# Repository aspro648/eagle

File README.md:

Repository to hold Eagle Cad design files I'm working on and sharing.

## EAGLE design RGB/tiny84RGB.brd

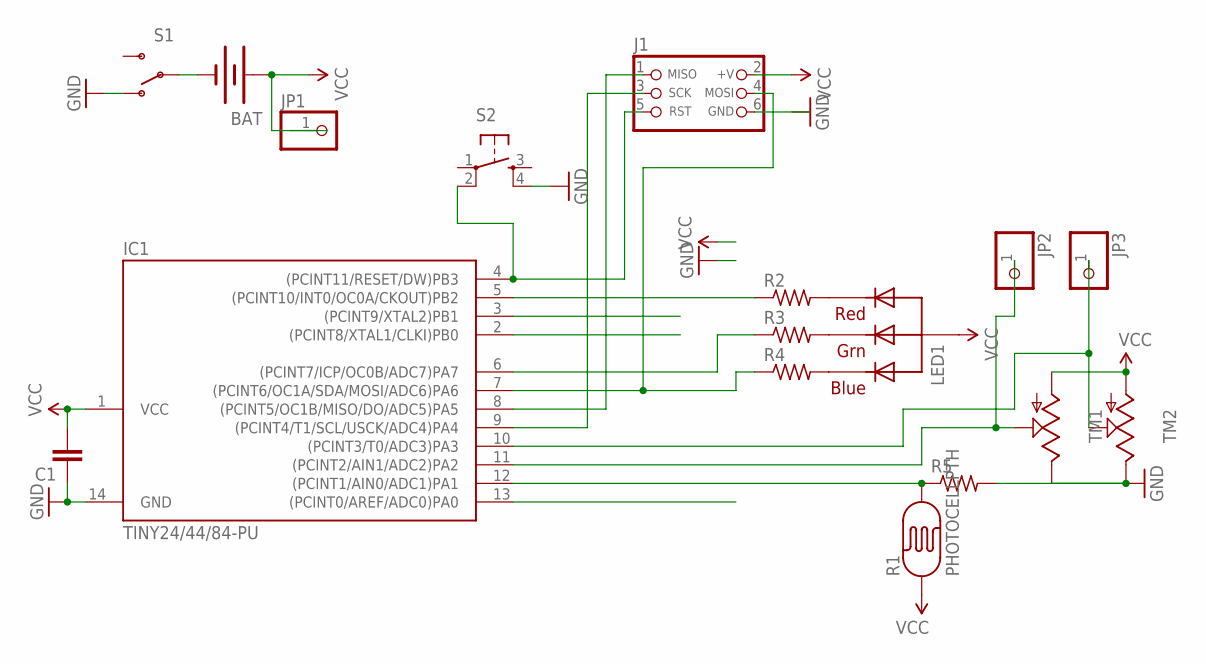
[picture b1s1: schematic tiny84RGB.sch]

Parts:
BAT: BATTERY20PTH; BATTCOM_20MM_PTH
C1: CAPKIT; CAP-PTH-SMALL-KIT
IC1: TINY24/44/84-PU; DIL14
J1: CON_HEADER_PRG_AVR_ICSP-PTH; HEADER_PRG_2X03
JP1, JP2, JP3: PINHD-1X1CB; 1X01-CLEANBIG
LED1: RGBLED_CA-5MM; LED5MMRGB
R1: PHOTOCELLPTH; PHOTOCELL
R2, R3, R4, R5: R-US_0204/7; 0204/7
S1: SWITCH-SPSTPTH; SWITCH-SPDT
S2: TAC_SWITCHPTH; TACTILE-PTH
TM1, TM2: TRIM; 6MM

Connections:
D0: IC1.13 ((PCINT0/AREF/ADC0)PA0)
D1: IC1.12 ((PCINT1/AIN0/ADC1)PA1), R1.2, R5.1
D2: IC1.11 ((PCINT2/AIN1/ADC2)PA2), JP2.1, TM1.S
D3: IC1.10 ((PCINT3/T0/ADC3)PA3), JP3.1, TM2.S
D4: IC1.9 ((PCINT4/T1/SCL/USCK/ADC4)PA4), J1.3 (SCK)
D5: IC1.8 ((PCINT5/OC1B/MISO/DO/ADC5)PA5), J1.1 (MISO)
D6: IC1.7 ((PCINT6/OC1A/SDA/MOSI/ADC6)PA6), J1.4 (MOSI), R4.1
D7: IC1.6 ((PCINT7/ICP/OC0B/ADC7)PA7), R3.1
D9: IC1.3 ((PCINT9/XTAL2)PB1)
D10: IC1.2 ((PCINT8/XTAL1/CLKI)PB0)
GND: C1.1, IC1.14 (GND), R5.2, S1.1 (O), S2.4, TM1.E, TM2.E
unnamed: BAT.2 (-), S1.2
unnamed: LED1.1 (RED), R2.2
unnamed: LED1.3 (GREEN), R3.2
unnamed: LED1.4 (BLUE), R4.2
unnamed: IC1.5 ((PCINT10/INT0/OC0A/CKOUT)PB2), R2.1
RESET: IC1.4 ((PCINT11/RESET/DW)PB3), J1.5 (RST), S2.2
VCC: BAT.1 (+), C1.2, IC1.1 (VCC), J1.2 (+V), JP1.1, LED1.2 (VCC), R1.1, TM1.A, TM2.A

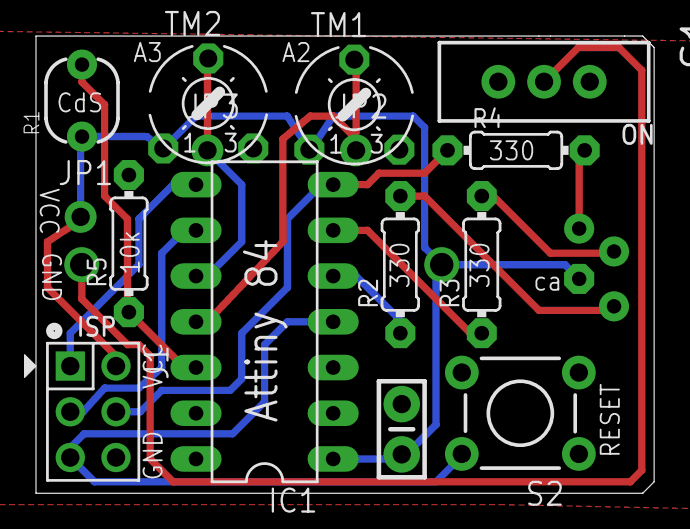
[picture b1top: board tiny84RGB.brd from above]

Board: 2 copper layers, 34.3 x 25.4 mm, 18 parts (1 on the bottom side), 15 nets.

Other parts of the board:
U$1: OREGON_18_52

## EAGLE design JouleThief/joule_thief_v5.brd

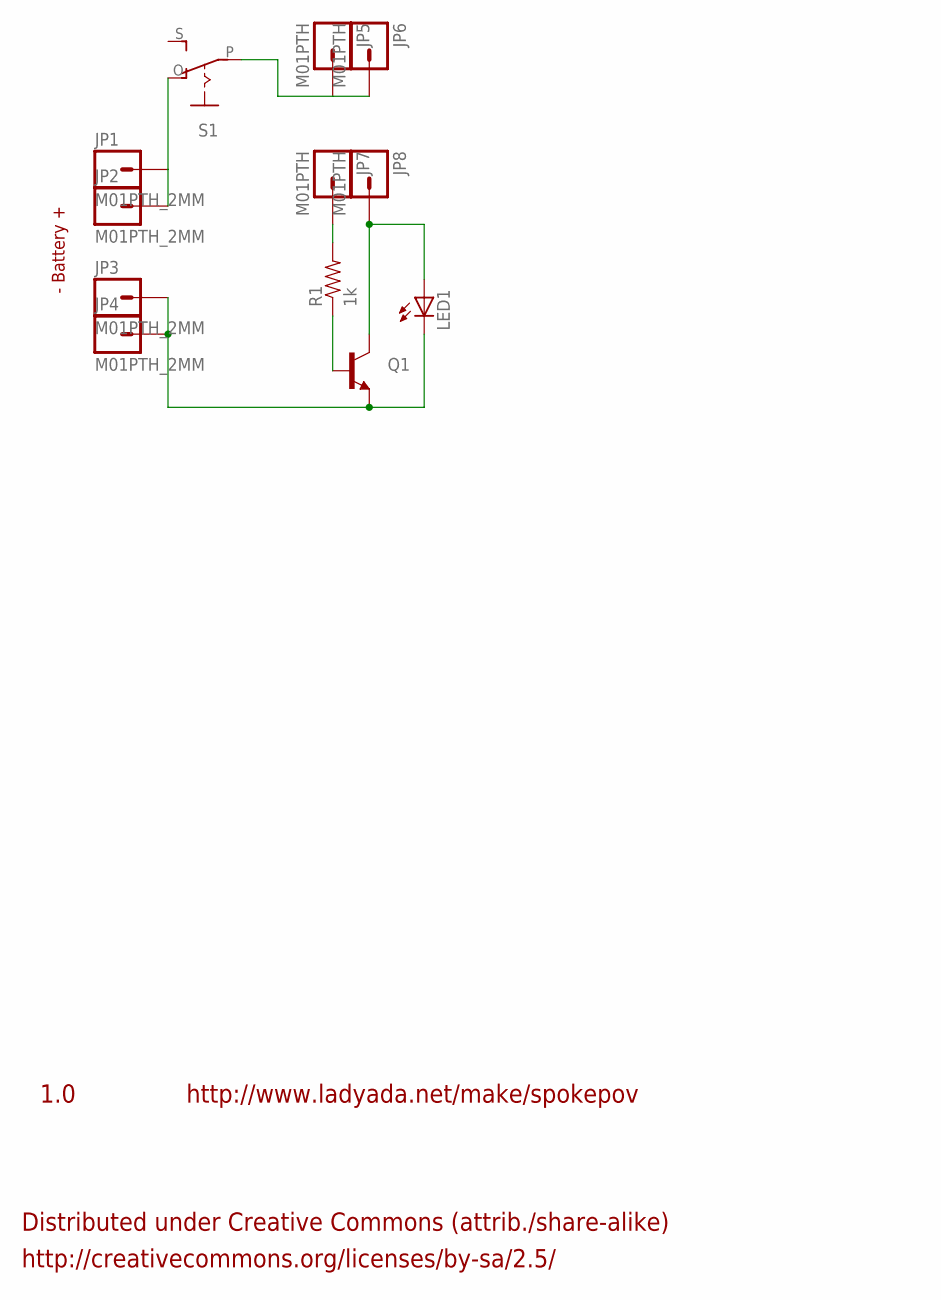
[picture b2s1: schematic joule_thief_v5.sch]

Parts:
JP1, JP2, JP3, JP4: M01PTH_2MM; 1X01_2MM
JP5, JP6, JP7, JP8: M01PTH; 1X01
LED1: LED5MM
Q1: TRANSISTOR_NPNTO-92-AMMO; TO-92-AMMO
R1: 1k; AXIAL-0.3
S1: EG1218S; EG1218

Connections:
unnamed: JP8.1, LED1.A, Q1.3 (C)
unnamed: JP7.1, R1.P$2 (2)
unnamed: Q1.2 (B), R1.P$1 (1)
unnamed: JP1.1, JP2.1, S1.O
unnamed: JP5.1, JP6.1, S1.P
unnamed: JP3.1, JP4.1, LED1.K (C), Q1.1 (E)

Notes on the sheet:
1.0
http://creativecommons.org/licenses/by-sa/2.5/
http://www.ladyada.net/make/spokepov
Distributed under Creative Commons (attrib./share-alike)
- Battery +

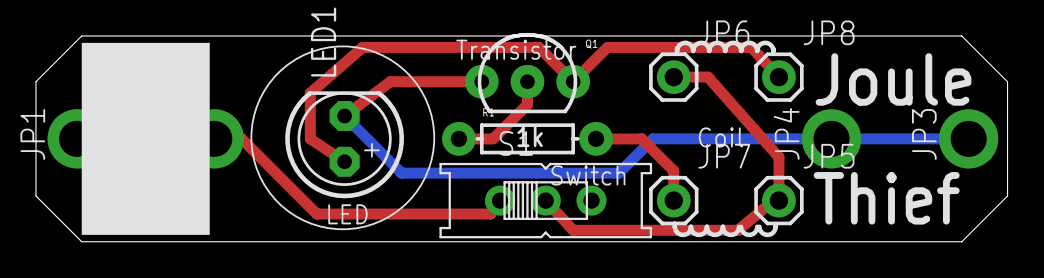
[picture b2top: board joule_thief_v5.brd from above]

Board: 2 copper layers, 54.0 x 11.4 mm, 12 parts (0 on the bottom side), 6 nets.

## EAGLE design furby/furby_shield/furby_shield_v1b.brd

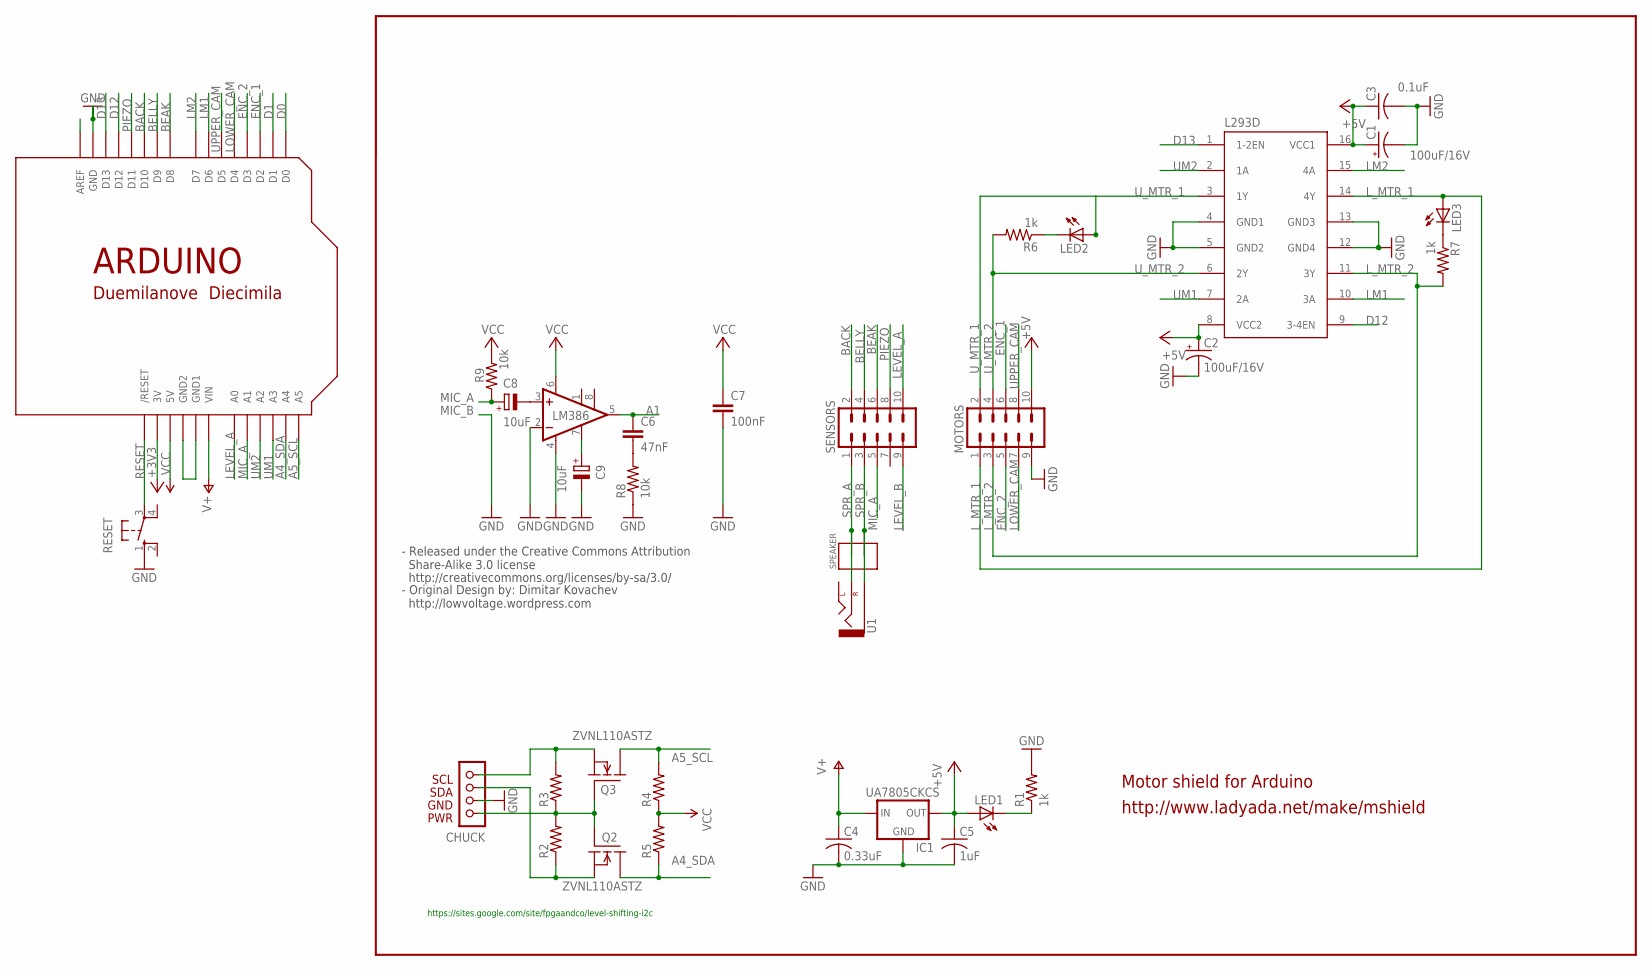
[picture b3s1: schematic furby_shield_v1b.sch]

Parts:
C1, C2: 100uF/16V; E2,5-6
C3: 0.1uF; C025-025X050
C4: 0.33uF; C025-024X044
C5: 1uF; C025-024X044
C6: 47nF; C025-030X050
C7: 100nF; C025-025X050
C8, C9: 10uF; E2,5-6
CHUCK: NUNCHUCK; CONN
IC1: UA7805CKCS; TO-220-ALT
L293D: L293E; DIL16
LED1, LED2, LED3: LED3MM
LM386: LM386N-1; DIL08
MOTORS: M05X2SHD; 2X5-SHROUDED
Q2, Q3: ZVNL110ASTZ; TO92-INLINE
R1, R6, R7: 1k; 0204/5
R2, R3, R4, R5: R-US_0204/7; 0204/7
R8, R9: 10k; 0204/7
RESET: 10-XX; B3F-10XX
SENSORS: M05X2SHD; 2X5-SHROUDED
SPEAKER: TERMINAL2; TERMINAL_2
U1: AUDIO-JACKPTH; AUDIO-JACK
U$1: ARDUINO-NOHOLE

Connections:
+3V3: CHUCK.PWR, Q2.2 (G), Q3.2 (G), R2.2, R3.1, U$1.3V
+5V: C1.+, C2.+, C3.1, C5.1, IC1.OUT, L293D.8 (VCC2), L293D.16 (VCC1), LED1.A, MOTORS.10
A1: C6.1, LM386.5 (OUT)
A4_SDA: Q2.1 (D), R5.1, U$1.A4
A5_SCL: Q3.1 (D), R4.2, U$1.A5
BACK: SENSORS.2, U$1.D10
BEAK: SENSORS.6, U$1.D8
BELLY: SENSORS.4, U$1.D9
D0: U$1.D0
D1: U$1.D1
D12: L293D.9 (3-4EN), U$1.D12
D13: L293D.1 (1-2EN), U$1.D13
ENC_1: MOTORS.6, U$1.D2
ENC_2: MOTORS.5, U$1.D3
GND: C1.-, C2.-, C3.2, C4.2, C5.2, C7.2, C9.-, CHUCK.GND, IC1.GND, L293D.4 (GND1), L293D.5 (GND2), L293D.12 (GND4), L293D.13 (GND3), LM386.2 (-IN), LM386.4 (GND), MOTORS.9, R1.2, R8.1, RESET.1 (S), U$1.GND, U$1.GND1, U$1.GND2
LEVEL_A: SENSORS.10, U$1.A0
LEVEL_B: SENSORS.9
LM1: L293D.10 (3A), U$1.D6
LM2: L293D.15 (4A), U$1.D7
LOWER_CAM: MOTORS.7, U$1.D4
L_MTR_1: L293D.14 (4Y), LED3.A, MOTORS.1
L_MTR_2: L293D.11 (3Y), MOTORS.3, R7.2
MIC_A: C8.+, R9.1, SENSORS.5, U$1.A1
unnamed: LED2.K (C), R6.1
unnamed: LED1.K (C), R1.1
unnamed: LED3.K (C), R7.1
unnamed: C6.2, R8.2
unnamed: C9.+, LM386.7 (BYPASS)
unnamed: C8.-, LM386.3 (+IN)
PIEZO: SENSORS.8, U$1.D11
RESET: RESET.3, U$1.RESET (/RESET)
SCL: CHUCK.SCL, Q3.3 (S), R3.2
SDA: CHUCK.SDA, Q2.3 (S), R2.1
SPR_A: SENSORS.1, SPEAKER.P$1, U1.RING (RIGHT)
SPR_B: SENSORS.3, SPEAKER.P$2, U1.SLEEVE
UM1: L293D.7 (2A), U$1.A3
UM2: L293D.2 (1A), U$1.A2
UPPER_CAM: MOTORS.8, U$1.D5
U_MTR_1: L293D.3 (1Y), LED2.A, MOTORS.2
U_MTR_2: L293D.6 (2Y), MOTORS.4, R6.2
V+: C4.1, IC1.IN, U$1.VIN
VCC: C7.1, LM386.6 (VS), R4.1, R5.2, R9.2, U$1.5V, U$1.AREF

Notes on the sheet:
Motor shield for Arduino
http://www.ladyada.net/make/mshield
https://sites.google.com/site/fpgaandco/level-shifting-i2c
- Original Design by: Dimitar Kovachev http://lowvoltage.wordpress.com
- Released under the Creative Commons Attribution Share-Alike 3.0 license
http://creativecommons.org/licenses/by-sa/3.0/

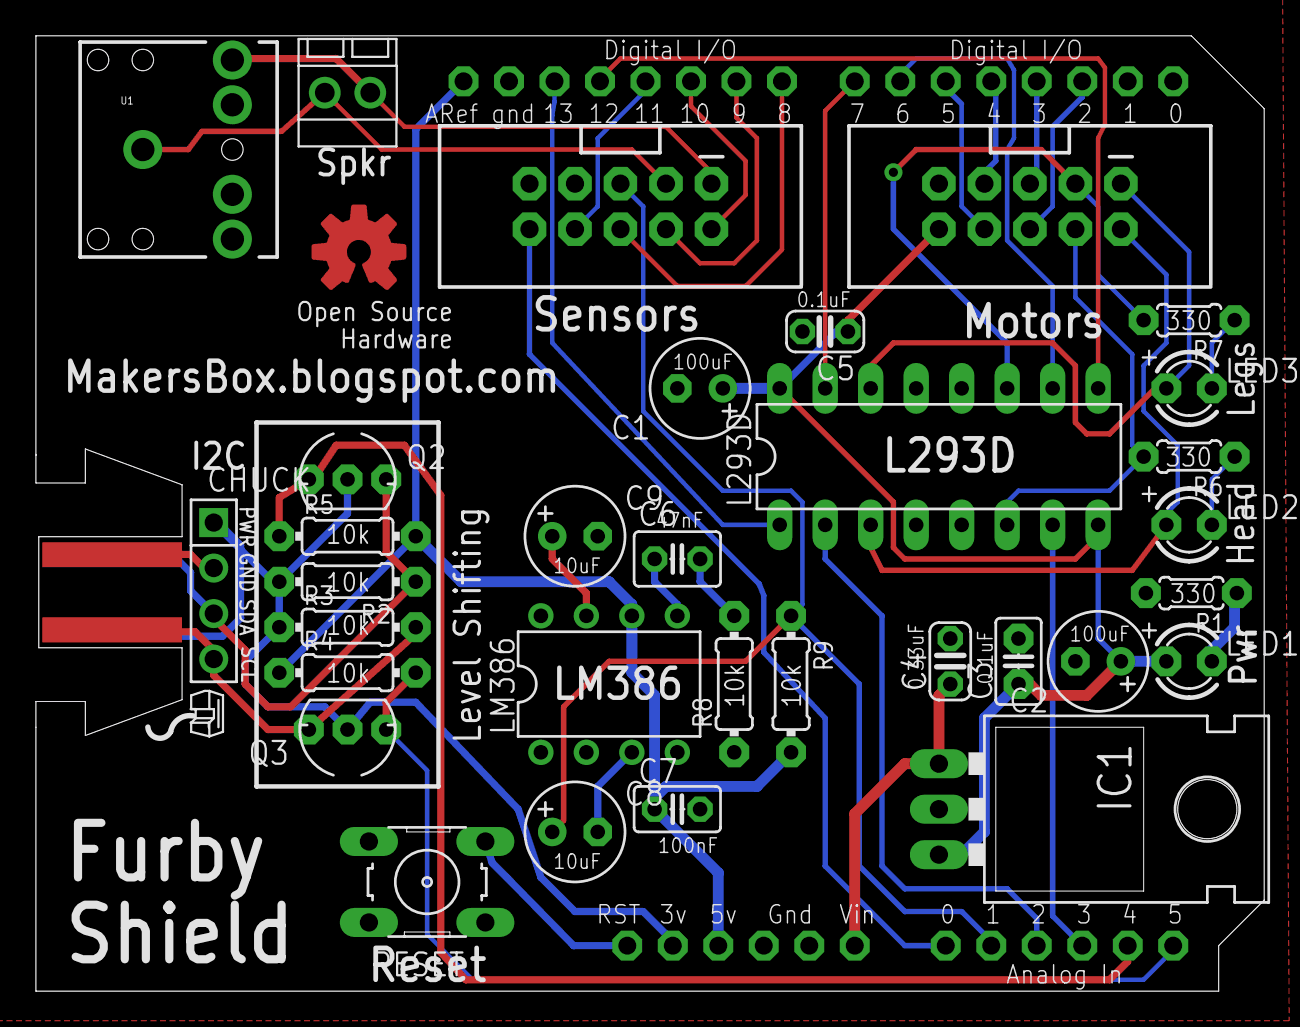
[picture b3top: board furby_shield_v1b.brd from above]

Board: 2 copper layers, 68.6 x 53.3 mm, 36 parts (0 on the bottom side), 39 nets.

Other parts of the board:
U$2: OSHWLOGO_TOP_0.2
U$3: OREGON_18_51
U$4: OREGON_18_52

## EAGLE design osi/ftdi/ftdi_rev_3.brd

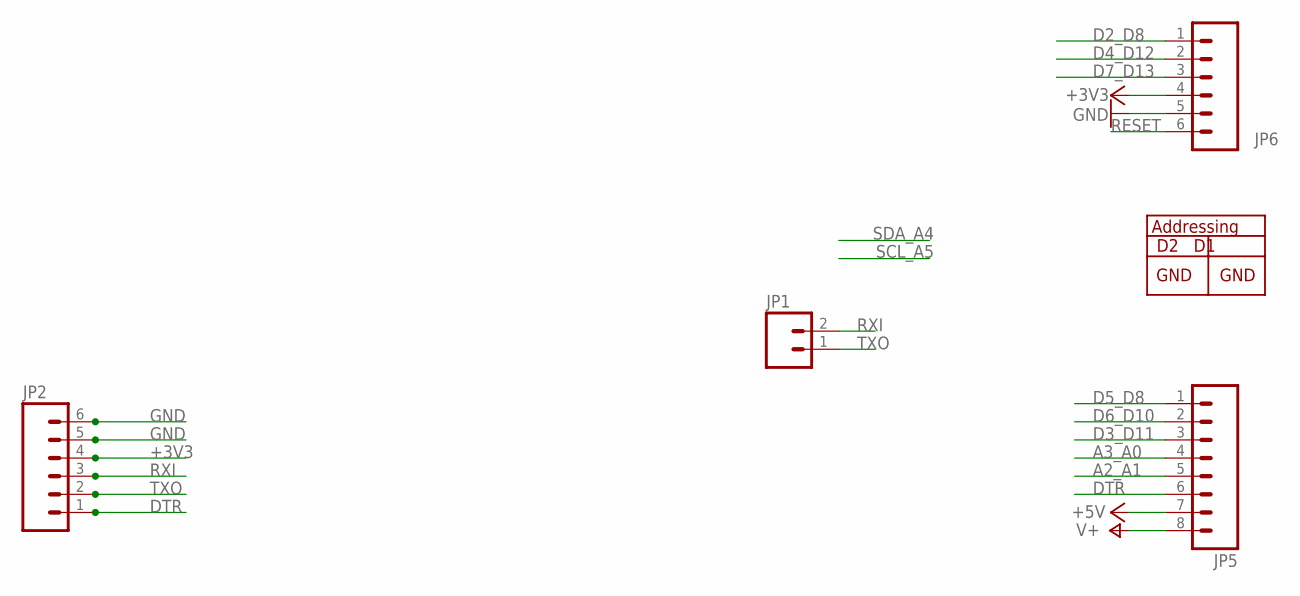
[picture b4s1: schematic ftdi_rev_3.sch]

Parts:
JP1: M02PTH; 1X02
JP2, JP6: M06SIP; 1X06
JP5: M081X08; 1X08

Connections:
+3V3: JP2.4, JP6.4
+5V: JP5.7
A2_A1: JP5.5
A3_A0: JP5.4
D2_D8: JP6.1
D3_D11: JP5.3
D4_D12: JP6.2
D5_D8: JP5.1
D6_D10: JP5.2
D7_D13: JP6.3
DTR: JP2.1, JP5.6
GND: JP2.5, JP2.6, JP6.5
RESET: JP6.6
RXI: JP1.2, JP2.3
TXO: JP1.1, JP2.2
V+: JP5.8

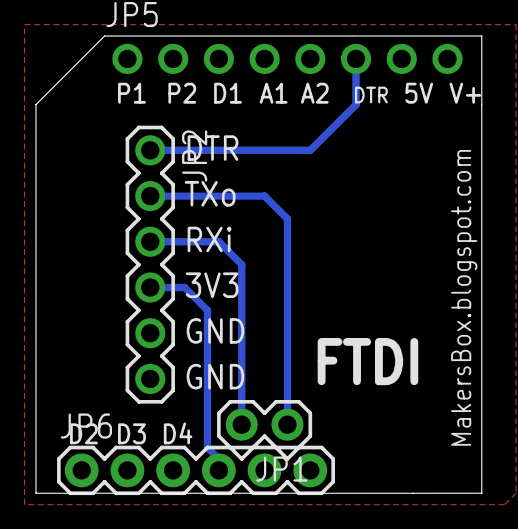
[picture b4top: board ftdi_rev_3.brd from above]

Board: 2 copper layers, 24.8 x 25.4 mm, 5 parts (0 on the bottom side), 5 nets.

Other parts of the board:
U$1: OREGON_18_52

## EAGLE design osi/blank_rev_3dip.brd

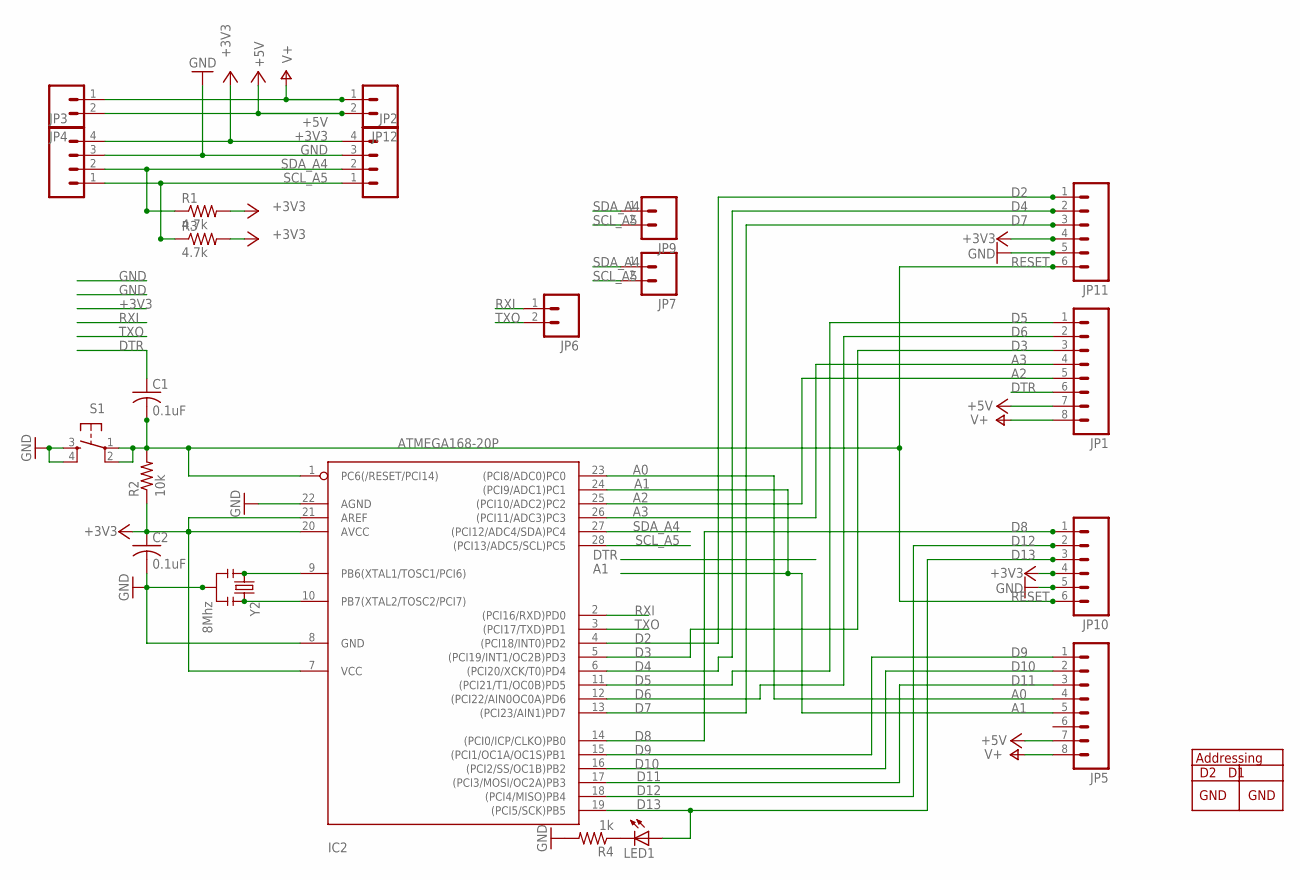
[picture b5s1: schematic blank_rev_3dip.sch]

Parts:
C1, C2: 0.1uF; C025-024X044
IC2: ATMEGA168-20P; DIL28-3
JP1, JP5: M081X08; 1X08
JP2, JP3: M04PTH; 1X04
JP4, JP6, JP7, JP9, JP12: M02PTH; 1X02
JP10, JP11: M06SIP; 1X06
LED1: LED3MM
R1, R3: 4.7k; 0204/7
R2: 10k; 0204/7
R4: 1k; 0204/7
S1: TAC_SWITCHPTH; TACTILE-PTH
Y2: 8Mhz; RESONATOR-PTH

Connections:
+3V3: C2.1, IC2.7 (VCC), IC2.20 (AVCC), IC2.21 (AREF), JP2.4, JP3.4, JP10.4, JP11.4, R1.2, R2.1, R3.2
+5V: JP1.7, JP4.2, JP5.7, JP12.2
A0: IC2.23 ((PCI8/ADC0)PC0), JP5.4
A1: IC2.24 ((PCI9/ADC1)PC1), JP5.5
A2: IC2.25 ((PCI10/ADC2)PC2), JP1.5
A3: IC2.26 ((PCI11/ADC3)PC3), JP1.4
D2: IC2.4 ((PCI18/INT0)PD2), JP11.1
D3: IC2.5 ((PCI19/INT1/OC2B)PD3), JP1.3
D4: IC2.6 ((PCI20/XCK/T0)PD4), JP11.2
D5: IC2.11 ((PCI21/T1/OC0B)PD5), JP1.1
D6: IC2.12 ((PCI22/AIN0OC0A)PD6), JP1.2
D7: IC2.13 ((PCI23/AIN1)PD7), JP11.3
D8: IC2.14 ((PCI0/ICP/CLKO)PB0), JP10.1
D9: IC2.15 ((PCI1/OC1A/OC1S)PB1), JP5.1
D10: IC2.16 ((PCI2/SS/OC1B)PB2), JP5.2
D11: IC2.17 ((PCI3/MOSI/OC2A)PB3), JP5.3
D12: IC2.18 ((PCI4/MISO)PB4), JP10.2
D13: IC2.19 ((PCI5/SCK)PB5), JP10.3, LED1.A
DTR: C1.1, JP1.6
GND: C2.2, IC2.8 (GND), IC2.22 (AGND), JP2.3, JP3.3, JP10.5, JP11.5, R4.2, S1.3, S1.4, Y2.2
unnamed: IC2.10 (PB7(XTAL2/TOSC2/PCI7)), Y2.3
unnamed: IC2.9 (PB6(XTAL1/TOSC1/PCI6)), Y2.1
unnamed: LED1.K (C), R4.1
RESET: C1.2, IC2.1 (PC6(/RESET/PCI14)), JP10.6, JP11.6, R2.2, S1.1, S1.2
RXI: IC2.2 ((PCI16/RXD)PD0), JP6.1
SCL_A5: IC2.28 ((PCI13/ADC5/SCL)PC5), JP2.1, JP3.1, JP7.2, JP9.2, R3.1
SDA_A4: IC2.27 ((PCI12/ADC4/SDA)PC4), JP2.2, JP3.2, JP7.1, JP9.1, R1.1
TXO: IC2.3 ((PCI17/TXD)PD1), JP6.2
V+: JP1.8, JP4.1, JP5.8, JP12.1

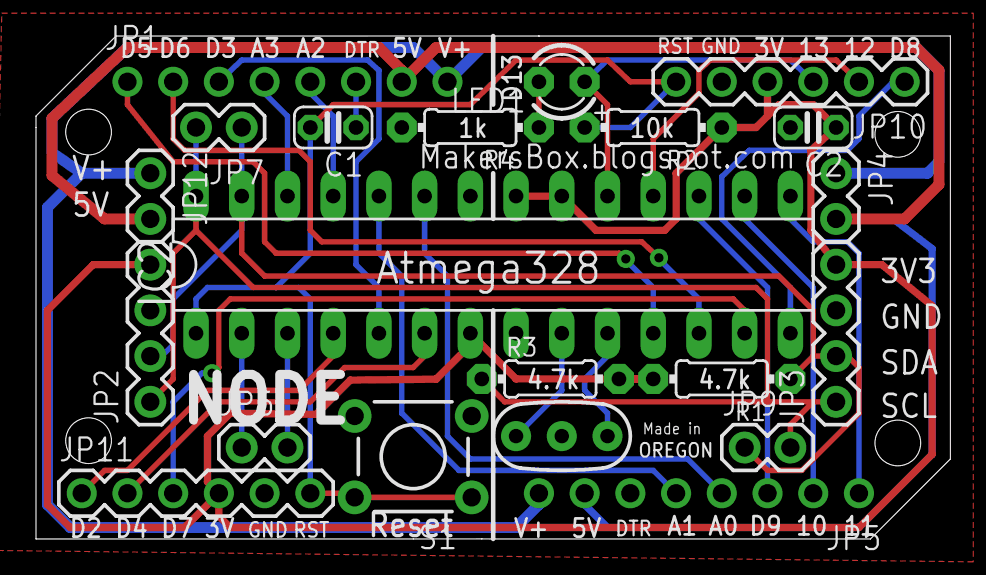
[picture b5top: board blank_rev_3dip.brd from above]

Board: 2 copper layers, 50.8 x 27.9 mm, 23 parts (0 on the bottom side), 29 nets.

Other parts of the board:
U$1: OREGON_24_52
U$2: OREGON_24_51

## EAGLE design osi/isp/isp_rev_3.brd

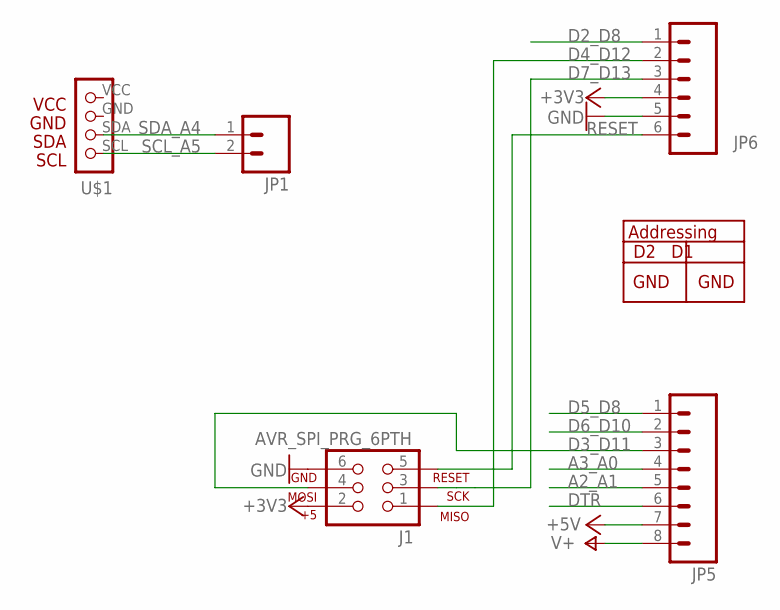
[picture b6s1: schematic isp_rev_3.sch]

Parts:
J1: AVR_SPI_PRG_6PTH; 2X3
JP1: M02PTH; 1X02
JP5: M081X08; 1X08
JP6: M06SIP; 1X06
U$1: NUNCHUCKCHUCK; CONN

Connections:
+3V3: J1.2, JP6.4
+5V: JP5.7
A2_A1: JP5.5
A3_A0: JP5.4
D2_D8: JP6.1
D3_D11: J1.4, JP5.3
D4_D12: J1.1, JP6.2
D5_D8: JP5.1
D6_D10: JP5.2
D7_D13: J1.3, JP6.3
DTR: JP5.6
GND: J1.6, JP6.5
RESET: J1.5, JP6.6
SCL_A5: JP1.2, U$1.SCL
SDA_A4: JP1.1, U$1.SDA
V+: JP5.8

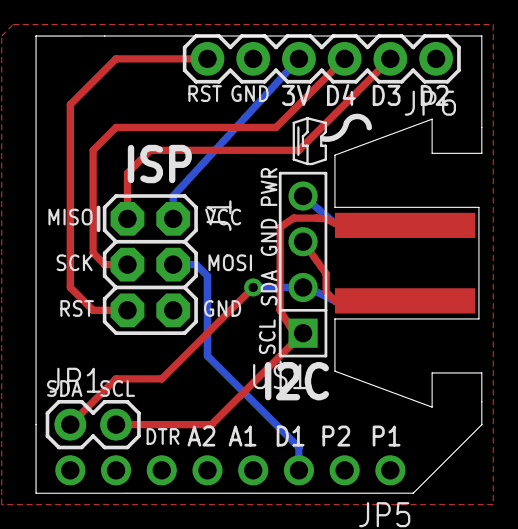
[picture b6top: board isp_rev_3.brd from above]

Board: 2 copper layers, 24.8 x 25.4 mm, 6 parts (0 on the bottom side), 8 nets.

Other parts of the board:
U$2: OREGON_18_52

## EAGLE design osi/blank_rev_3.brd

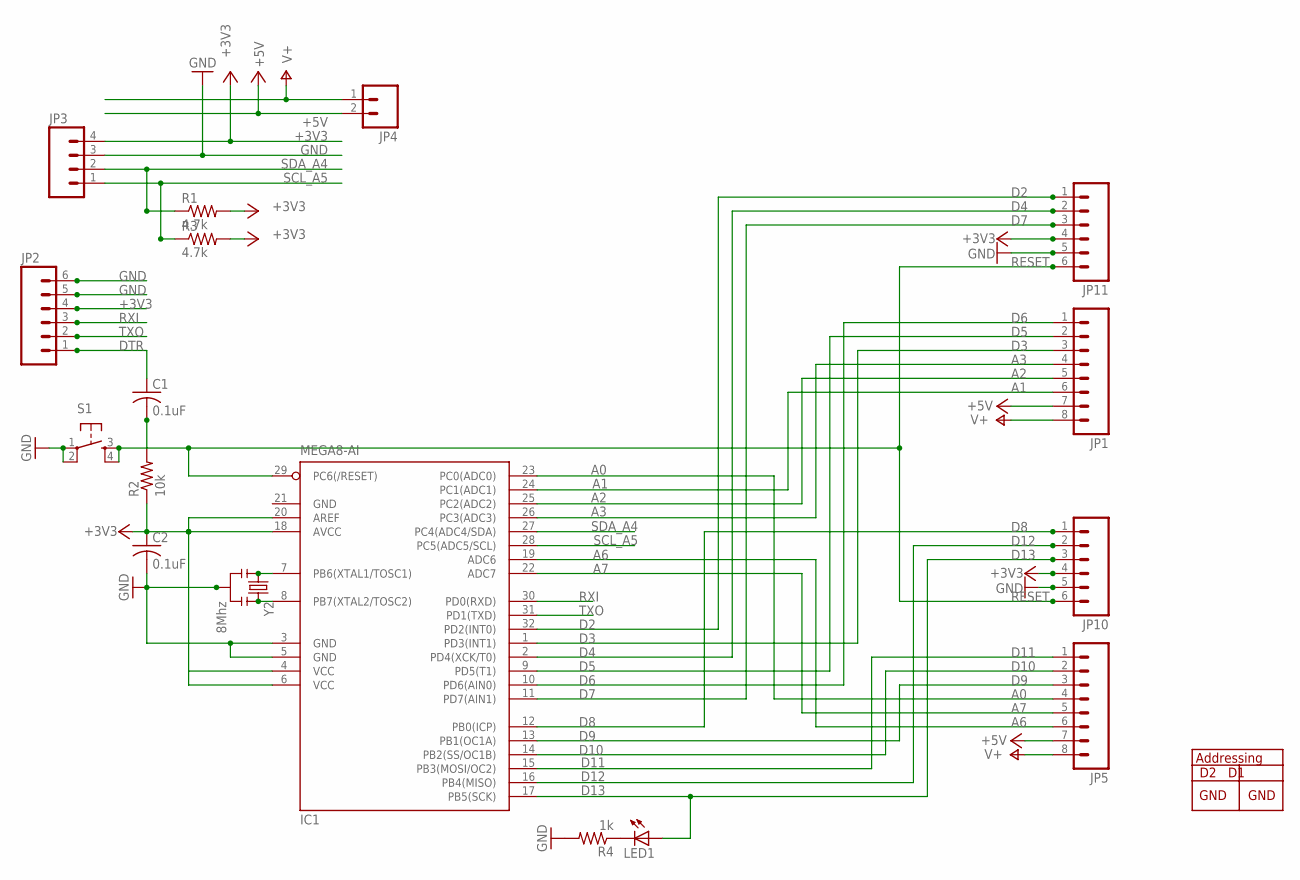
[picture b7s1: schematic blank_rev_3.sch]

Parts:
C1, C2: 0.1uF; C025-024X044
IC1: MEGA8-AI; TQFP32-08
JP1, JP5: M081X08; 1X08
JP2, JP10, JP11: M06SIP; 1X06
JP3: M04PTH; 1X04
JP4: M02PTH; 1X02
LED1: LED3MM
R1, R3: 4.7k; 0204/7
R2: 10k; 0204/7
R4: 1k; 0204/7
S1: TAC_SWITCHPTH; TACTILE-PTH
Y2: 8Mhz; RESONATOR-PTH

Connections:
+3V3: C2.1, IC1.4 (VCC), IC1.6 (VCC), IC1.18 (AVCC), IC1.20 (AREF), JP2.4, JP3.4, JP10.4, JP11.4, R1.2, R2.1, R3.2
+5V: JP1.7, JP4.2, JP5.7
A0: IC1.23 (PC0(ADC0)), JP5.4
A1: IC1.24 (PC1(ADC1)), JP1.6
A2: IC1.25 (PC2(ADC2)), JP1.5
A3: IC1.26 (PC3(ADC3)), JP1.4
A6: IC1.19 (ADC6), JP5.6
A7: IC1.22 (ADC7), JP5.5
D2: IC1.32 (PD2(INT0)), JP11.1
D3: IC1.1 (PD3(INT1)), JP1.3
D4: IC1.2 (PD4(XCK/T0)), JP11.2
D5: IC1.9 (PD5(T1)), JP1.2
D6: IC1.10 (PD6(AIN0)), JP1.1
D7: IC1.11 (PD7(AIN1)), JP11.3
D8: IC1.12 (PB0(ICP)), JP10.1
D9: IC1.13 (PB1(OC1A)), JP5.3
D10: IC1.14 (PB2(SS/OC1B)), JP5.2
D11: IC1.15 (PB3(MOSI/OC2)), JP5.1
D12: IC1.16 (PB4(MISO)), JP10.2
D13: IC1.17 (PB5(SCK)), JP10.3, LED1.A
DTR: C1.1, JP2.1
GND: C2.2, IC1.3 (GND), IC1.5 (GND), IC1.21 (GND), JP2.5, JP2.6, JP3.3, JP10.5, JP11.5, R4.2, S1.1, S1.2, Y2.2
unnamed: IC1.8 (PB7(XTAL2/TOSC2)), Y2.3
unnamed: IC1.7 (PB6(XTAL1/TOSC1)), Y2.1
unnamed: LED1.K (C), R4.1
RESET: C1.2, IC1.29 (PC6(/RESET)), JP10.6, JP11.6, R2.2, S1.3, S1.4
RXI: IC1.30 (PD0(RXD)), JP2.3
SCL_A5: IC1.28 (PC5(ADC5/SCL)), JP3.1, R3.1
SDA_A4: IC1.27 (PC4(ADC4/SDA)), JP3.2, R1.1
TXO: IC1.31 (PD1(TXD)), JP2.2
V+: JP1.8, JP4.1, JP5.8

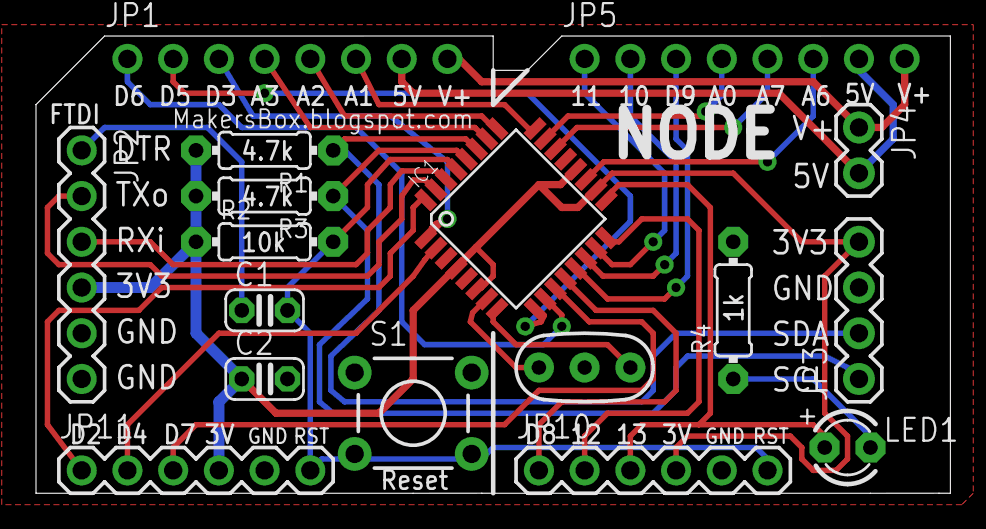
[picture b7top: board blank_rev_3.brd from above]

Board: 2 copper layers, 50.8 x 25.4 mm, 19 parts (0 on the bottom side), 31 nets.

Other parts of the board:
U$1: OREGON_09_52
U$2: OREGON_18_51

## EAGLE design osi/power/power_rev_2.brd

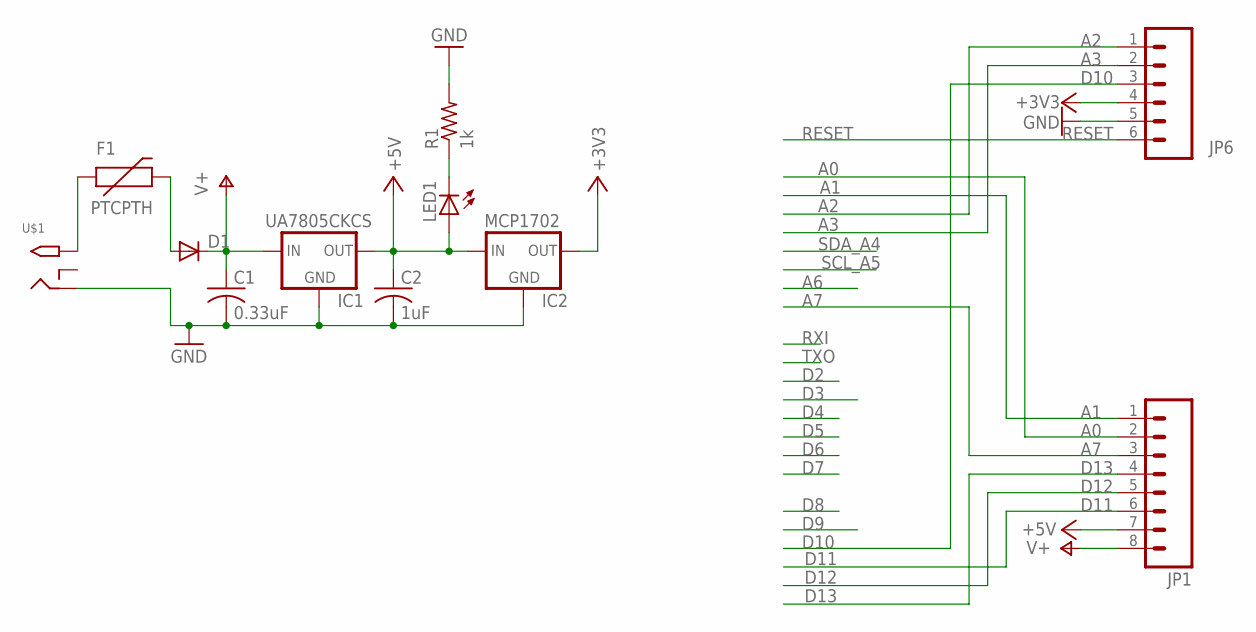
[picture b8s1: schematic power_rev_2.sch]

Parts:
C1: 0.33uF; C025-024X044
C2: 1uF; C025-024X044
D1: DIODE1N4148; DIODE-1N4148
F1: PTCPTH; PTC
IC1: UA7805CKCS; TO-220-ALT
IC2: MCP1702; TO92-INLINE
JP1: M081X08; 1X08
JP6: M06SIP; 1X06
LED1: LED3MM
R1: 1k; 0204/5
U$1: 2.1MMJACKTHM; PJ-102A

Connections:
+3V3: IC2.3 (OUT), JP6.4
+5V: C2.1, IC1.OUT, IC2.2 (IN), JP1.7, LED1.A
A0: JP1.2
A1: JP1.1
A2: JP6.1
A3: JP6.2
A7: JP1.3
D10: JP6.3
D11: JP1.6
D12: JP1.5
D13: JP1.4
GND: C1.2, C2.2, IC1.GND, IC2.1 (GND), JP6.5, R1.2, U$1.RING
unnamed: F1.P$1 (1), U$1.TIP
unnamed: LED1.K (C), R1.1
unnamed: D1.A, F1.P$2 (2)
RESET: JP6.6
V+: C1.1, D1.C, IC1.IN, JP1.8

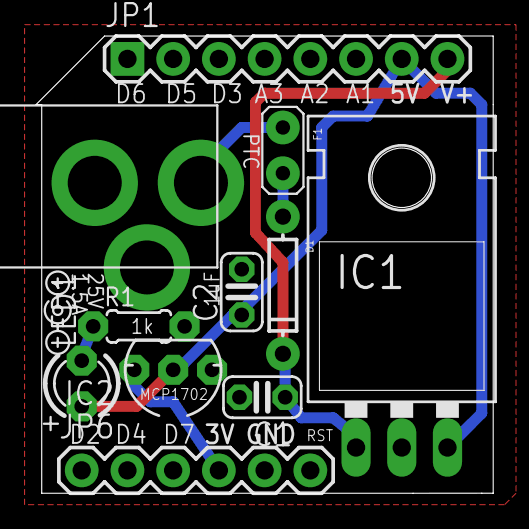
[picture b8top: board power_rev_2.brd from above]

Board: 2 copper layers, 25.4 x 25.4 mm, 13 parts (0 on the bottom side), 7 nets.

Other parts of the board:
U$2: DC_POS_CTR
U$3: DC_POS_CTR-BOTTOM

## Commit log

2013-01-09 adding avr_programmer files
2013-01-09 adding files again?
2013-01-09 Update after lunch session.
2013-01-10 Adding pdf of schematic and bill of materials
2013-01-11 Added some text saying "DaveO was here to schematic view"
2013-01-11 Test file
2013-01-11 Testing git - added some txt
2013-01-11 ANother test
2013-01-11 Removed one doubled up line of text
2013-01-11 Added reset cap and resonator, fixed ISP_84 MISO line.
2013-01-11 Test
2013-01-11 testing again
    test test test
2013-01-11 test
    test
2013-01-11 Adding this to deal with CR/LF on Eagle files
2013-01-11 Pushing from dorth-z400
2013-01-11 Push
2013-01-11 Adding my versions - independent of main branch
2013-01-11 Removed blink LED, added Mega jumper.
2013-01-11 DaveO Fixed: Missing junction in net GND (Arduino GND1/GND2) Fixed: Missing junction in net N$11 (ZIF PIN# 7) Fixed: Removed wire from Arduino VIN pin as it was not connected to anything
2013-01-11 Removing test.txt file
2013-01-12 Updated BOM
2013-01-12 Tweaked component layout.
2013-01-14 Pushing again
2013-01-16 adding pinout.svg
2013-01-16 updating setting for svg files
2013-01-17 Adding Bill's fine layout work.
2013-01-22 updating Zif footprint
2013-01-22 modified part libraries with smaller pads
2013-02-04 updated bill of materials and adding uploaded build files
2013-02-19 updated .gitignore for CAM files
2013-02-19 add new project
2013-02-21 routing a diffrent setup
2013-02-25 changing directory structure
2013-02-25 file cleanup
2013-02-26 directory
2013-02-26 cleanup:
2013-02-26 adding Bill14
2013-02-27 working on brain
2013-02-27 brain
2013-02-27 power-ac
2013-02-28 brain batt cleanup
2013-02-28 control brain
2013-03-01 cleanup
2013-03-02 chuck
2013-03-02 control
2013-03-07 D9 -> D8 for INT0
2013-03-10 rev 1 manufacture
2013-04-02 adding JouleThief
2013-04-03 v1.2 board
2013-04-04 Moving RST line in brain
2013-04-04 continue on brain
2013-04-08 Programming shield ver 1.2
2013-04-10 adding isp
2013-04-11 328 TFOP?
2013-04-11 328p surface mount
2013-04-13 layout changes
2013-04-18 Furby
2013-04-24 Furby work
2013-04-28 Furby shield
2013-05-01 furby updates
2013-05-07 furby board production
2013-05-08 moving headers
2013-05-10 Leguino
2013-05-12 double board finished?
2013-05-21 Joule Thief V5
2013-06-20 trying a commit

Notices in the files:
parts and their libraries:
SparkFun-DiscreteSemi: Licensing: CC v3.0 Share-Alike You are welcome to use this library for commercial purposes.
